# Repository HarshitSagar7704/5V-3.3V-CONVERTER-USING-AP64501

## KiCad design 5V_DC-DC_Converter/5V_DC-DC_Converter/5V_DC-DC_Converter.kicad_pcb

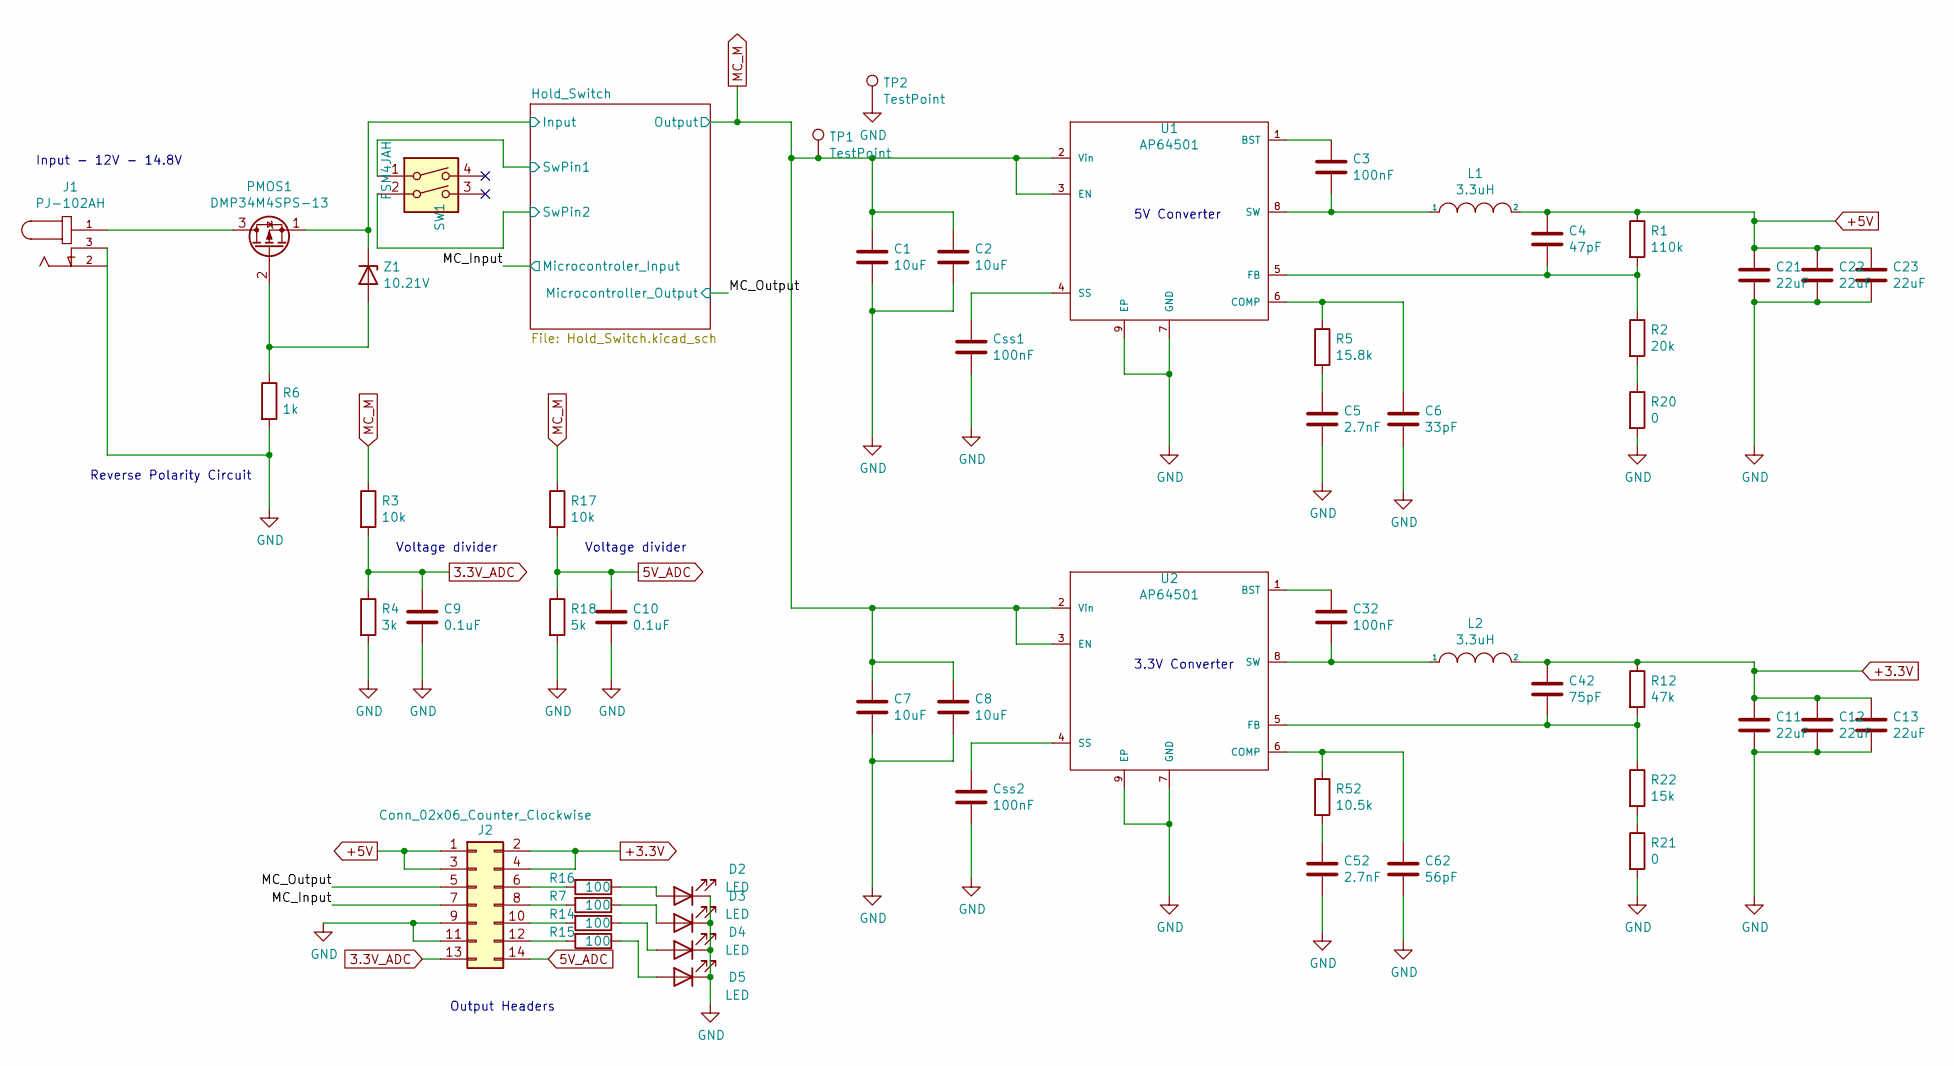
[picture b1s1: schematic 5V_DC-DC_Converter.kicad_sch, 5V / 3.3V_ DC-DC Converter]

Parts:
C1, C2, C7, C8: 10uF; C_0805_2012Metric
C3, C32: 100nF; C_0805_2012Metric
C4: 47pF; C_0805_2012Metric
C5, C52: 2.7nF; C_0805_2012Metric
C6: 33pF; C_0805_2012Metric
C9, C10: 0.1uF; C_0805_2012Metric
C11, C12, C13, C21, C22, C23: 22uF; C_0805_2012Metric
C42: 75pF; C_0805_2012Metric
C62: 56pF; C_0805_2012Metric
Css1, Css2: 100nF; C_0805_2012Metric
D2, D3, D4, D5: LED; LED_0805_2012Metric
J1: PJ-102AH; BarrelJack_CUI_PJ-102AH_Horizontal; MPN PJ-102AH
J2: Conn_02x06_Counter_Clockwise; PinHeader_2x07_P2.54mm_Vertical
L1, L2: 3.3uH; SRN6045TA330M; MPN SRN6045TA-3R3Y
PMOS1: DMP34M4SPS-13; DMP3M4SPS-13_1; MPN DMP34M4SPS-13
R1: 110k; R_0805_2012Metric
R2: 20k; R_0805_2012Metric
R3, R17: 10k; R_0805_2012Metric
R4: 3k; R_0805_2012Metric
R5: 15.8k; R_0805_2012Metric
R6: 1k; R_0805_2012Metric
R7, R14, R15, R16: 100; R_0805_2012Metric
R12: 47k; R_0805_2012Metric
R18: 5k; R_0805_2012Metric
R20, R21: 0; R_0805_2012Metric
R22: 15k; R_0805_2012Metric
R52: 10.5k; R_0805_2012Metric
SW1: FSM4JAH; SW_PUSH_6mm; MPN FSM4JAH
TP1, TP2: TestPoint; TestPoint_Pad_2.0x2.0mm
U1, U2: AP64501; SOIC-8-1EP_3.9x4.9mm_P1.27mm_EP2.95x4.9mm_Mask2.71x3.4mm; MPN AP64501SP-13
Z1: 10.21V; D_SOD-523; MPN EDZVT2R9.1B

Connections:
3.3V_ADC: C9.1, J2.13, R3.2, R4.1
5V_ADC: C10.1, J2.14, R17.2, R18.1
+3.3V: C11.1, C12.1, C13.1, C42.1, J2.2, J2.4, L2.2, R12.1
+5V: C4.1, C21.1, C22.1, C23.1, J2.1, J2.3, L1.2, R1.1
/Hold_Switch/Input: PMOS1.1 (S), SW1.1, Z1.1 (K); also elsewhere on the board
/Hold_Switch/SwPin2: SW1.2; also elsewhere on the board
/MC_Input: J2.7; also elsewhere on the board
/MC_Output: J2.5; also elsewhere on the board
GND: C1.2, C2.2, C5.2, C6.2, C7.2, C8.2, C9.2, C10.2, C11.2, C12.2, C13.2, C21.2, C22.2, C23.2, C52.2, C62.2, Css1.2, Css2.2, D2.1 (K), D3.1 (K), D4.1 (K), D5.1 (K), J1.3, J2.9, J2.11, R4.2, R6.2, R18.2, R20.2, R21.2, TP2.1, U1.7 (GND), U1.9 (EP), U2.7 (GND), U2.9 (EP); also elsewhere on the board
MC_M: C1.1, C2.1, C7.1, C8.1, R3.1, R17.1, TP1.1, U1.2 (Vin), U1.3 (EN), U2.2 (Vin), U2.3 (EN); also elsewhere on the board
unnamed: C3.1, U1.1 (BST)
unnamed: C3.2, L1.1, U1.8 (SW)
unnamed: C4.2, R1.2, R2.1, U1.5 (FB)
unnamed: C5.1, R5.2
unnamed: C6.1, R5.1, U1.6 (COMP)
unnamed: C32.1, U2.1 (BST)
unnamed: C32.2, L2.1, U2.8 (SW)
unnamed: C42.2, R12.2, R22.1, U2.5 (FB)
unnamed: C52.1, R52.2
unnamed: C62.1, R52.1, U2.6 (COMP)
unnamed: Css1.1, U1.4 (SS)
unnamed: Css2.1, U2.4 (SS)
unnamed: D2.2 (A), R16.1
unnamed: D3.2 (A), R7.1
unnamed: D4.2 (A), R14.1
unnamed: D5.2 (A), R15.1
unnamed: J1.1, PMOS1.3 (D)
unnamed: J2.6, R16.2
unnamed: J2.8, R7.2
unnamed: J2.10, R14.2
unnamed: J2.12, R15.2
unnamed: R2.2, R20.1
unnamed: PMOS1.2 (G), R6.1, Z1.2 (A)
unnamed: R21.1, R22.2

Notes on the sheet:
Input - 12V - 14.8V
Reverse Polarity Circuit
Voltage divider
Output Headers
5V Converter
3.3V Converter

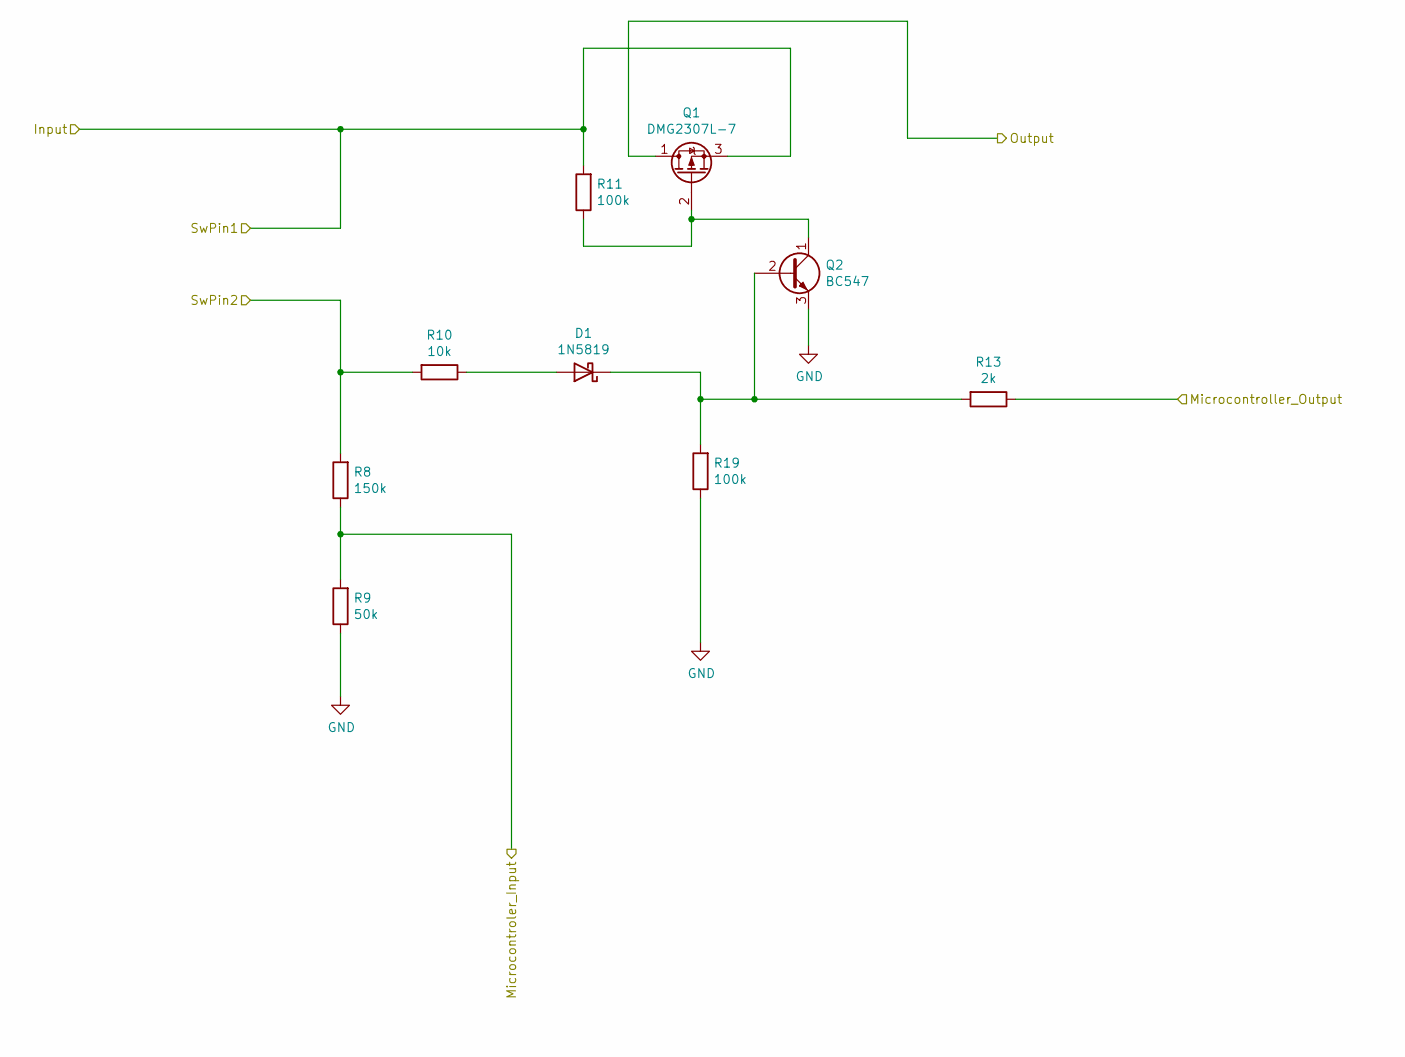
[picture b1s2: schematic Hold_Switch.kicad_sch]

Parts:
D1: 1N5819; D_SOD-123; MPN 1N5819HW-7-F
Q1: DMG2307L-7; SOT-23; MPN DMG2307L-7
Q2: BC547; TO-92_Inline; MPN BC547B
R8: 150k; R_0805_2012Metric
R9: 50k; R_0805_2012Metric
R10: 10k; R_0805_2012Metric
R11, R19: 100k; R_0805_2012Metric
R13: 2k; R_0805_2012Metric

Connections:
/Hold_Switch/Input: Q1.3 (S), R11.2; also elsewhere on the board
/Hold_Switch/SwPin2: R8.2, R10.2; also elsewhere on the board
/MC_Input: R8.1, R9.2; also elsewhere on the board
/MC_Output: R13.1; also elsewhere on the board
GND: Q2.3 (E), R9.1, R19.1; also elsewhere on the board
MC_M: Q1.1 (D); also elsewhere on the board
unnamed: D1.1 (K), Q2.2 (B), R13.2, R19.2
unnamed: D1.2 (A), R10.1
unnamed: Q1.2 (G), Q2.1 (C), R11.1

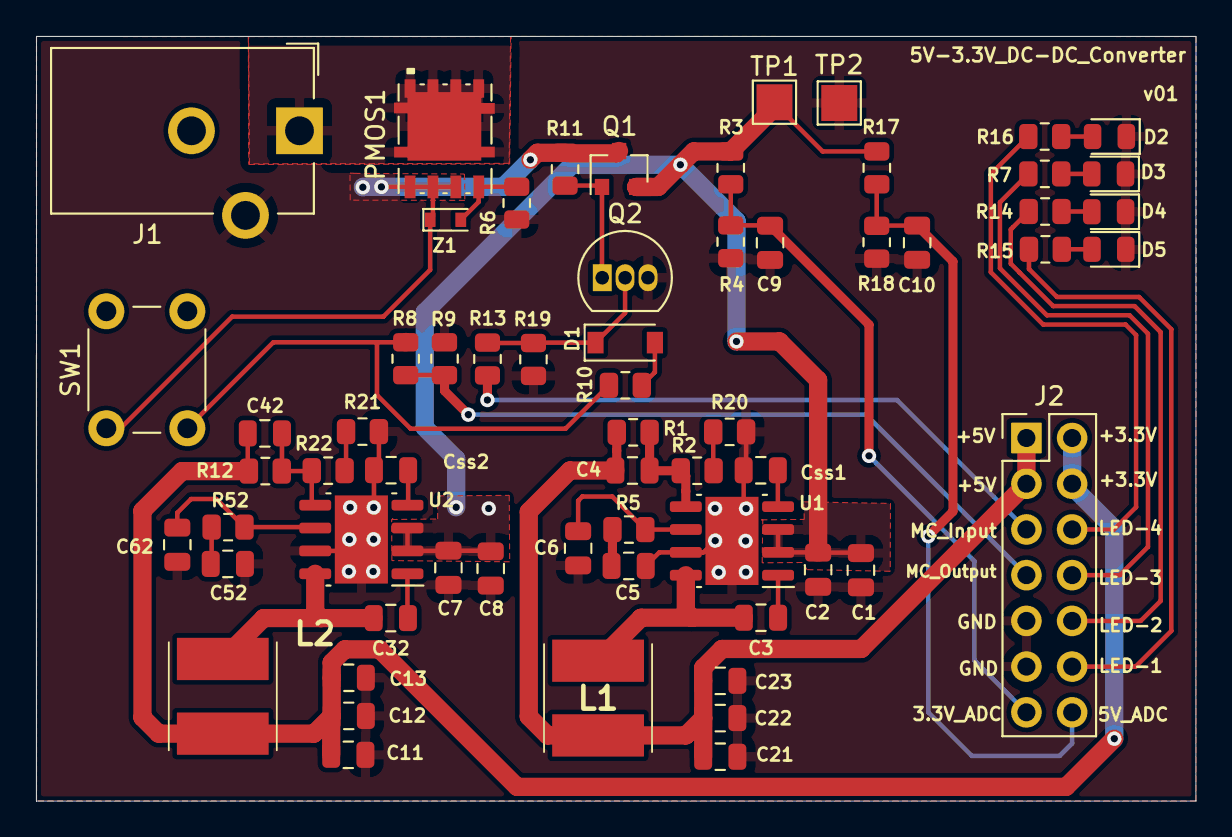
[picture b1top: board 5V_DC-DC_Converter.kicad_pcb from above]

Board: 2 copper layers, 64.4 x 42.5 mm, 63 parts (0 on the bottom side), 37 nets.

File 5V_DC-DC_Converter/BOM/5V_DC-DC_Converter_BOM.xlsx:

Reference | Value | Footprint | Datasheet | Comment | Description | MPN | Quantity
Z1 | 10.21V | 5V_DC-DC_Converter:D_SOD-523 | https://www.mouser.in/datasheet/2/348/edzvt2r9.1b-e-1870924.pdf |  | Zener Diodes Diode Zener Sgl 9.04V 150mW | EDZVT2R9.1B | 1
U2,U1 | AP64501 | Package_SO:SOIC-8-1EP_3.9x4.9mm_P1.27mm_EP2.95x4.9mm_Mask2.71x3.4mm | https://www.diodes.com/assets/Datasheets/AP64501.pdf |  | Switching Voltage Regulators DCDC Conv HV Buck SO-8EP T&R 4K | AP64501SP-13 | 2
TP2 | TestPoint | TestPoint:TestPoint_Pad_2.0x2.0mm | ~ |  |  |  | 1
TP1 | TestPoint | TestPoint:TestPoint_Pad_2.0x2.0mm | ~ |  |  |  | 1
SW1 | FSM4JAH | 5V_DC-DC_Converter:SW_PUSH_6mm | https://www.mouser.in/datasheet/2/418/NG_CD_1825910_C10-660299.pdf |  | Tactile Switches TACTILE SWITCH 6MM HIGH | FSM4JAH | 1
R52 | 10.5k | Resistor_SMD:R_0805_2012Metric | ~ |  |  |  | 1
R22 | 15k | Resistor_SMD:R_0805_2012Metric |  | Tolerance Should be as minimum as you can.. | Thin Film Resistors 0805 0.05% 22.1Kohm 10ppm SMD | ERA-6VRW2212V | 1
R21,R20 | 0 | Resistor_SMD:R_0805_2012Metric | ~ | Tolerance Should be as minimum as you can.. | Thin Film Resistors 0805 0.05% 22.1Kohm 10ppm SMD | ERA-6VRW2212V | 2
R19 | 100k | Resistor_SMD:R_0805_2012Metric | ~ |  |  |  | 1
R18 | 5k | Resistor_SMD:R_0805_2012Metric | ~ |  |  |  | 1
R17 | 10k | Resistor_SMD:R_0805_2012Metric | ~ |  |  |  | 1
R16 | 100 | Resistor_SMD:R_0805_2012Metric | ~ |  |  |  | 1
R15 | 100 | Resistor_SMD:R_0805_2012Metric | ~ |  |  |  | 1
R14 | 100 | Resistor_SMD:R_0805_2012Metric | ~ |  |  |  | 1
R13 | 2k | Resistor_SMD:R_0805_2012Metric | ~ |  |  |  | 1
R12 | 47k | Resistor_SMD:R_0805_2012Metric | ~ | Tolerance Should be as minimum as you can.. | Thin Film Resistors 0805 0.05% 69.8Kohm 10ppm SMD | ERA-6VRW6982V | 1
R11 | 100k | Resistor_SMD:R_0805_2012Metric | ~ |  |  |  | 1
R10 | 10k | Resistor_SMD:R_0805_2012Metric | ~ |  |  |  | 1
R9 | 50k | Resistor_SMD:R_0805_2012Metric | ~ |  |  |  | 1
R8 | 150k | Resistor_SMD:R_0805_2012Metric | ~ |  |  |  | 1
R7 | 100 | Resistor_SMD:R_0805_2012Metric | ~ |  |  |  | 1
R6 | 1k | Resistor_SMD:R_0805_2012Metric | ~ |  |  |  | 1
R5 | 15.8k | Resistor_SMD:R_0805_2012Metric | ~ |  |  |  | 1
R4 | 3k | Resistor_SMD:R_0805_2012Metric | ~ |  |  |  | 1
R3 | 10k | Resistor_SMD:R_0805_2012Metric | ~ |  |  |  | 1
R2 | 20k | Resistor_SMD:R_0805_2012Metric | ~ | Tolerance Should be as minimum as you can.. | Thin Film Resistors 0805 0.05% 22.1Kohm 10ppm SMD | ERA-6VRW2212V | 1
R1 | 110k | Resistor_SMD:R_0805_2012Metric | ~ | Tolerance Should be as minimum as you can.. | Thin Film Resistors 1/8W 115K Ohms 0.05% 0805 10ppm | RG2012N-1153-W-T5 | 1
Q2 | BC547 | Package_TO_SOT_THT:TO-92_Inline | https://www.onsemi.com/pub/Collateral/BC550-D.pdf |  | Bipolar Transistors - BJT NPN 45V 100mA HFE/45 | BC547B | 1
Q1 | DMG2307L-7 | 5V_DC-DC_Converter:SOT-23 | https://www.mouser.in/datasheet/2/115/DMG2307L-1101173.pdf |  | MOSFET MOSFET BVDSS: 25V-30 25V-30V,SOT23,3K | DMG2307L-7 | 1
PMOS1 | DMP34M4SPS-13 | 5V_DC-DC_Converter:DMP3M4SPS-13_1 | https://www.mouser.in/datasheet/2/115/DMP34M4SPS-1288849.pdf |  | MOSFET MOSFET BVDSS: 25V-30V | DMP34M4SPS-13 | 1
L2,L1 | 3.3uH | 5V_DC-DC_Converter:SRN6045TA330M | https://www.mouser.in/datasheet/2/54/srn6045ta-1391592.pdf |  | Fixed Inductors 3.3uH 30% 4.5A shd SMD AEC-Q200 | SRN6045TA-3R3Y | 2
J2 | Conn_02x06_Counter_Clockwise | Connector_PinHeader_2.54mm:PinHeader_2x07_P2.54mm_Vertical | ~ |  |  |  | 1
J1 | PJ-102AH | Connector_BarrelJack:BarrelJack_CUI_PJ-102AH_Horizontal | https://www.mouser.in/datasheet/2/670/pj_102ah-1778518.pdf |  | DC Power Connectors Power Jacks | PJ-102AH | 1
D5 | LED | LED_SMD:LED_0805_2012Metric | ~ |  |  |  | 1
D4 | LED | LED_SMD:LED_0805_2012Metric | ~ |  |  |  | 1
D3 | LED | LED_SMD:LED_0805_2012Metric | ~ |  |  |  | 1
D2 | LED | LED_SMD:LED_0805_2012Metric | ~ |  |  |  | 1
D1 | 1N5819 | Diode_SMD:D_SOD-123 | https://www.mouser.in/datasheet/2/115/ds30217-1532212.pdf |  | Schottky Diodes & Rectifiers Vr/40V Io/1A T/R | 1N5819HW-7-F | 1
Css2,Css1 | 100nF | Capacitor_SMD:C_0805_2012Metric | ~ |  |  |  | 2
C62 | 56pF | Capacitor_SMD:C_0805_2012Metric | ~ |  |  |  | 1
C52 | 2.7nF | Capacitor_SMD:C_0805_2012Metric | ~ |  |  |  | 1
C42 | 75pF | Capacitor_SMD:C_0805_2012Metric | ~ |  |  |  | 1
C32 | 100nF | Capacitor_SMD:C_0805_2012Metric | ~ |  |  |  | 1
C23,C22,C21,C13,C12,C11 | 22uF | Capacitor_SMD:C_0805_2012Metric | ~ |  |  |  | 6
C10,C9 | 0.1uF | Capacitor_SMD:C_0805_2012Metric | ~ |  |  |  | 2
C8,C7,C2,C1 | 10uF | Capacitor_SMD:C_0805_2012Metric | ~ |  |  |  | 4
C6 | 33pF | Capacitor_SMD:C_0805_2012Metric | ~ |  |  |  | 1
C5 | 2.7nF | Capacitor_SMD:C_0805_2012Metric | ~ |  |  |  | 1
C4 | 47pF | Capacitor_SMD:C_0805_2012Metric | ~ |  |  |  | 1
C3 | 100nF | Capacitor_SMD:C_0805_2012Metric | ~ |  |  |  | 1

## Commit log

2021-09-06 Added libraries folder
2021-09-06 Deleted extra folder
2021-10-29 Updated PCB

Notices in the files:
parts and their libraries:
Copyright 2021 Accelerated Designs. All rights reserved.
